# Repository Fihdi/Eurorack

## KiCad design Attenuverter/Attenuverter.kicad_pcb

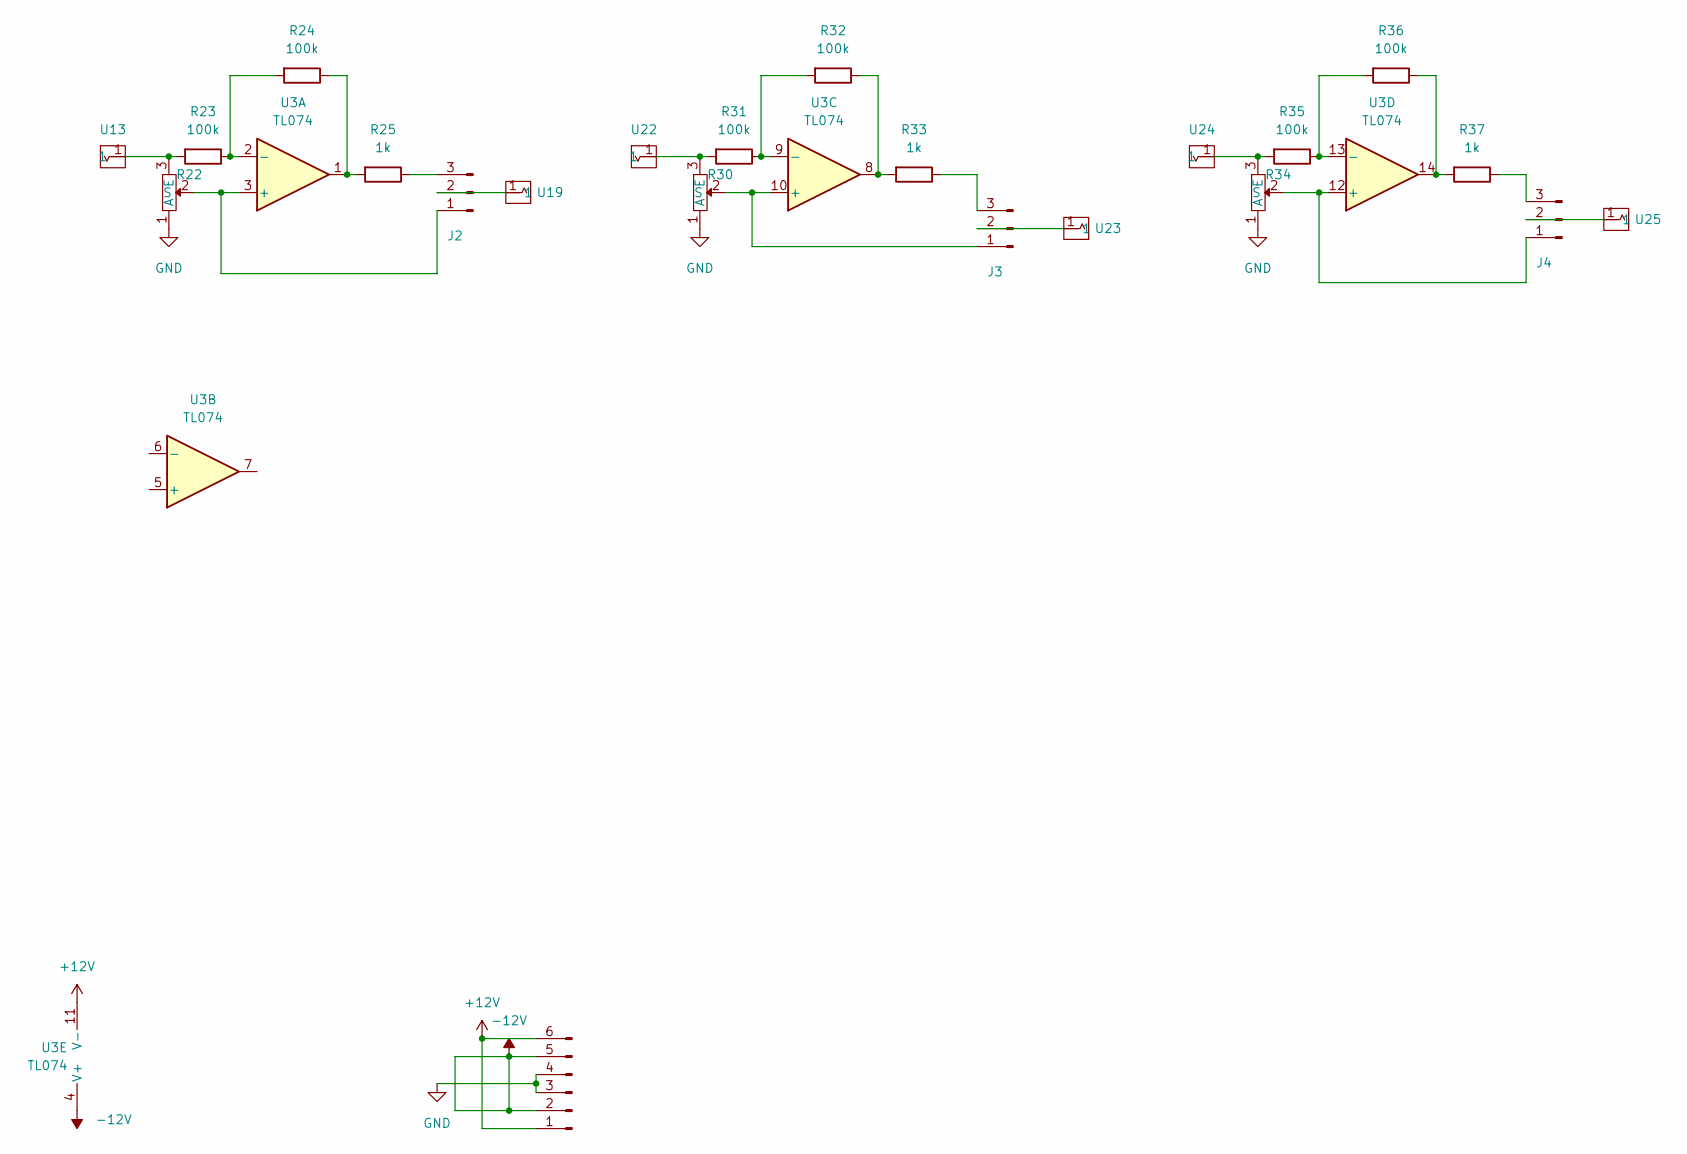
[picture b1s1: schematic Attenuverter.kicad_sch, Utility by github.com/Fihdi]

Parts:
J1: Conn_01x06_Male; PinHeader_1x06_P2.54mm_Vertical
J2, J3, J4: Conn_01x03_Pin; PinSocket_1x03_P2.54mm_Vertical
R22, R30, R34: AlpsPot
R23, R24, R31, R32, R35, R36: 100k; R_Axial_DIN0207_L6.3mm_D2.5mm_P7.62mm_Horizontal
R25, R33, R37: 1k; R_Axial_DIN0207_L6.3mm_D2.5mm_P7.62mm_Horizontal
U3: TL074; DIP-14_W7.62mm
U13, U19, U22, U23, U24, U25: Aux_flush; 3mm5 Mono Aux

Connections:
+12V: J1.1, J1.6, U3.11 (V-)
-12V: J1.2, J1.5, U3.4 (V+)
GND: J1.3, J1.4, R22.1 (A), R30.1 (A), R34.1 (A)
unnamed: J2.1, R22.2 (S), U3.3 (+)
unnamed: J2.2, U19.1
unnamed: J2.3, R25.1
unnamed: J3.1, R30.2 (S), U3.10 (+)
unnamed: J3.2, U23.1
unnamed: J3.3, R33.1
unnamed: J4.1, R34.2 (S), U3.12 (+)
unnamed: J4.2, U25.1
unnamed: J4.3, R37.1
unnamed: R22.3 (E), R23.2, U13.1
unnamed: R24.1, R25.2, U3.1
unnamed: R30.3 (E), R31.2, U22.1
unnamed: R32.1, R33.2, U3.8
unnamed: R34.3 (E), R35.2, U24.1
unnamed: R36.1, R37.2, U3.14
unnamed: R23.1, R24.2, U3.2 (-)
unnamed: R31.1, R32.2, U3.9 (-)
unnamed: R35.1, R36.2, U3.13 (-)

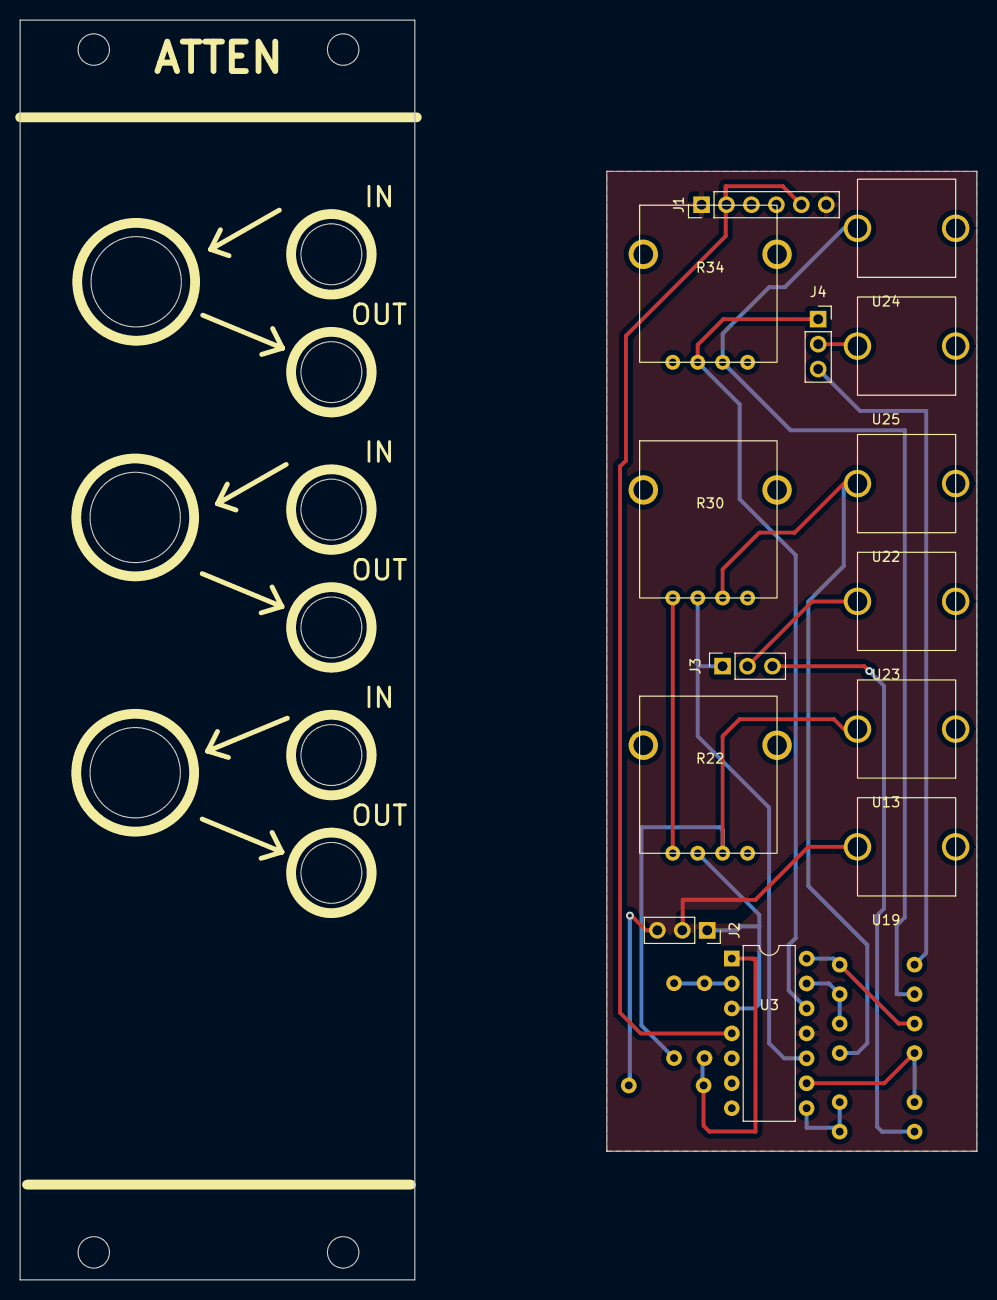
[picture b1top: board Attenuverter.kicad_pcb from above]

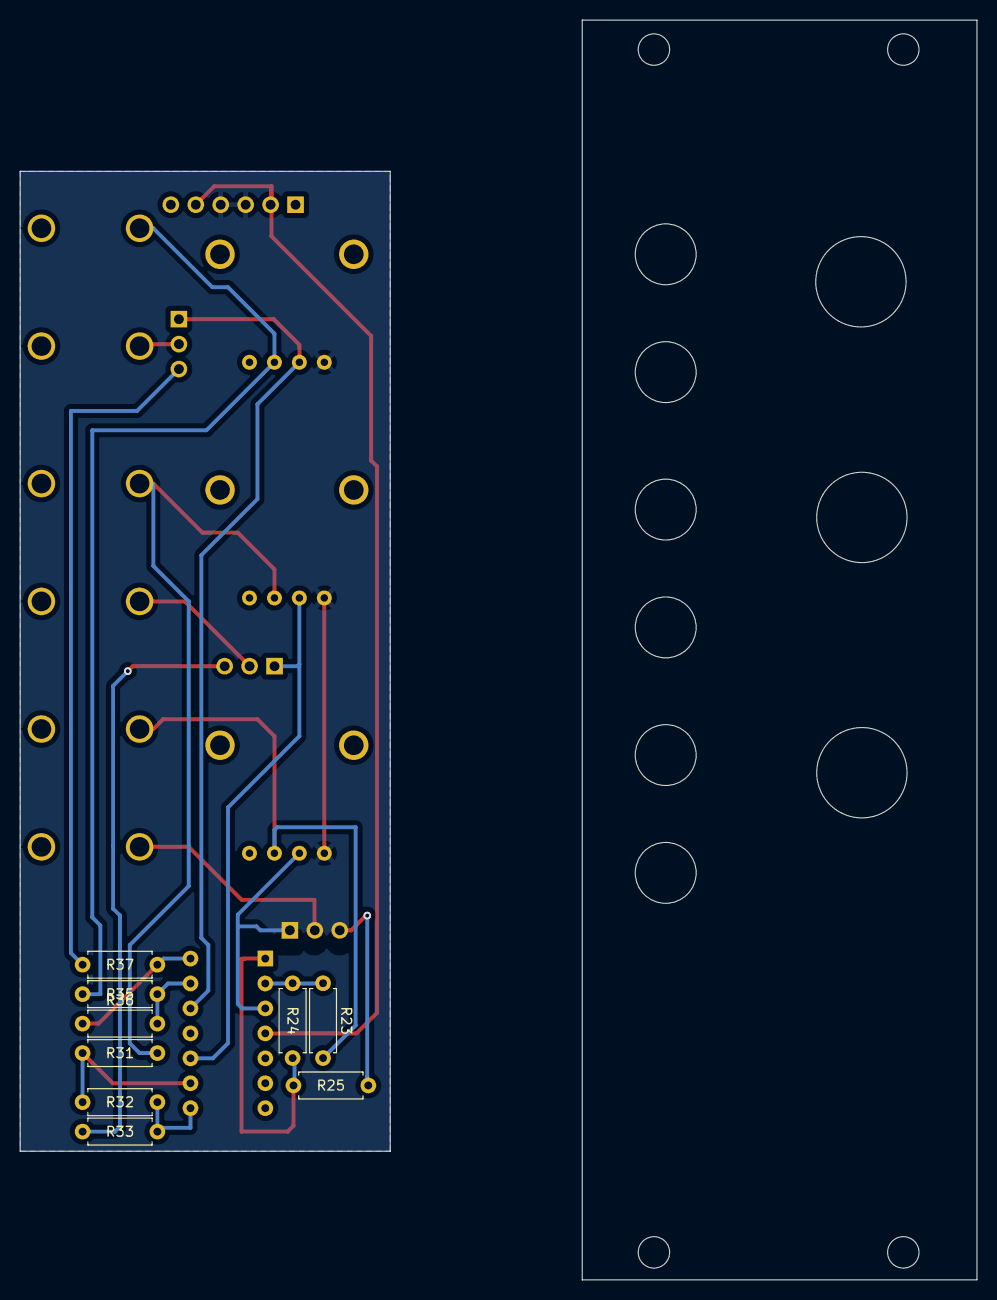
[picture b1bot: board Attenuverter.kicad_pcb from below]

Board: 2 copper layers, 37.7 x 99.8 mm, 23 parts (9 on the bottom side), 21 nets.

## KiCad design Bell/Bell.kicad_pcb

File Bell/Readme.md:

Bell Module with voltage control over decay time and accent.

Two square wave oscillators are summed together and put through a bandpass filter and a VCA. Choose the capacitor sizes of the filters and oscillators to your own liking.

No voltage control over the two square wave generator frequencies.

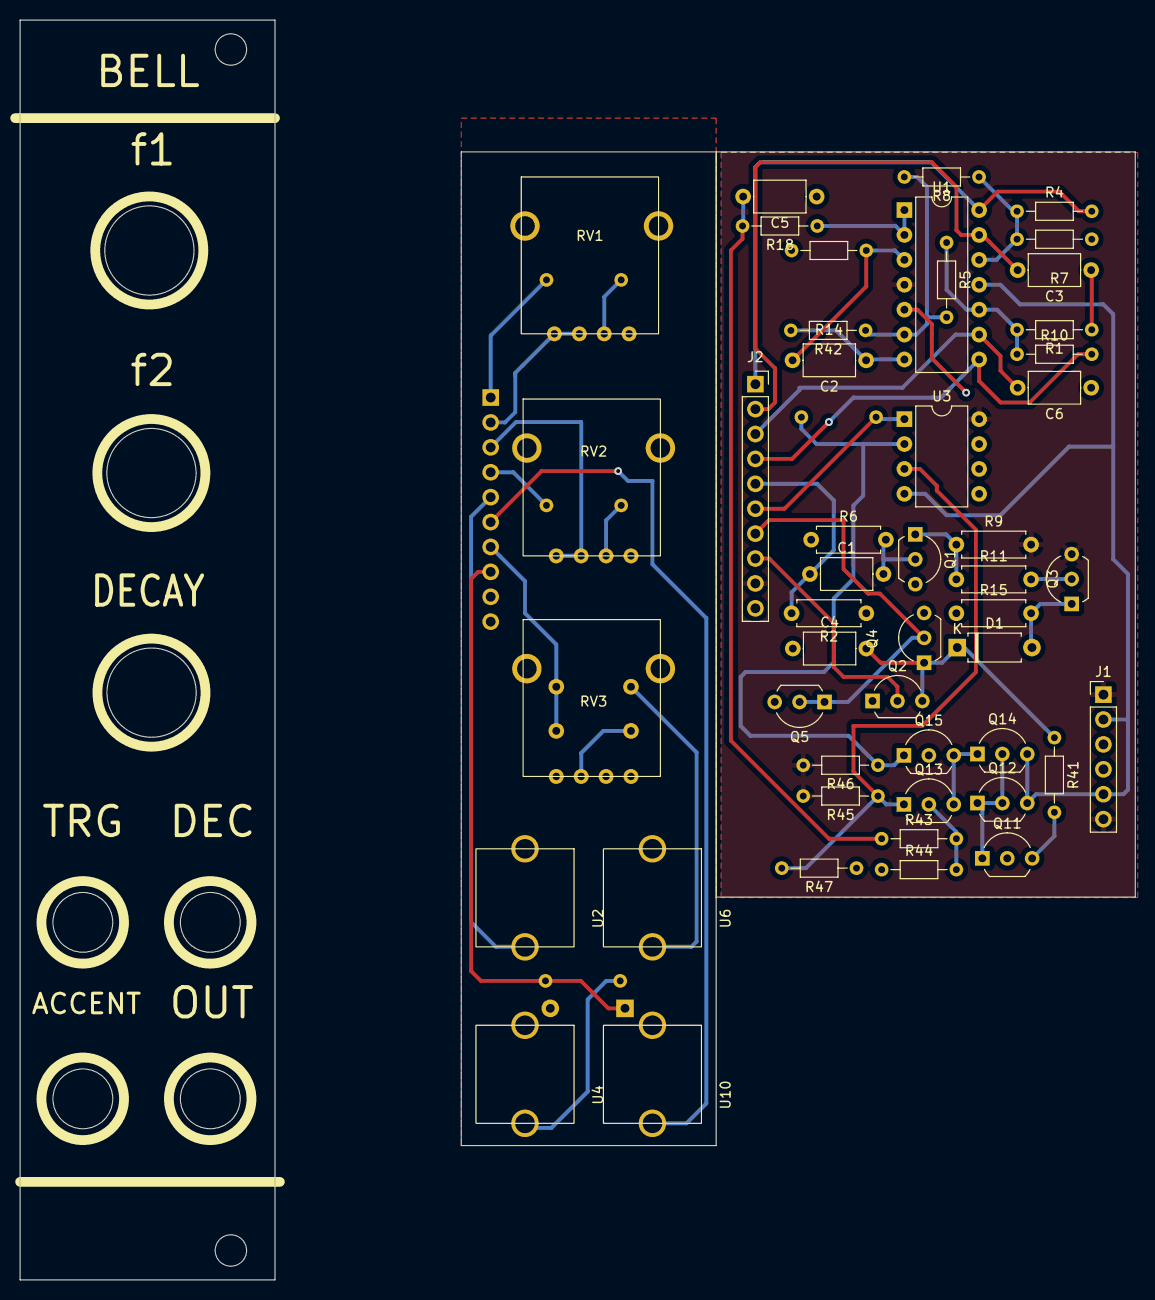
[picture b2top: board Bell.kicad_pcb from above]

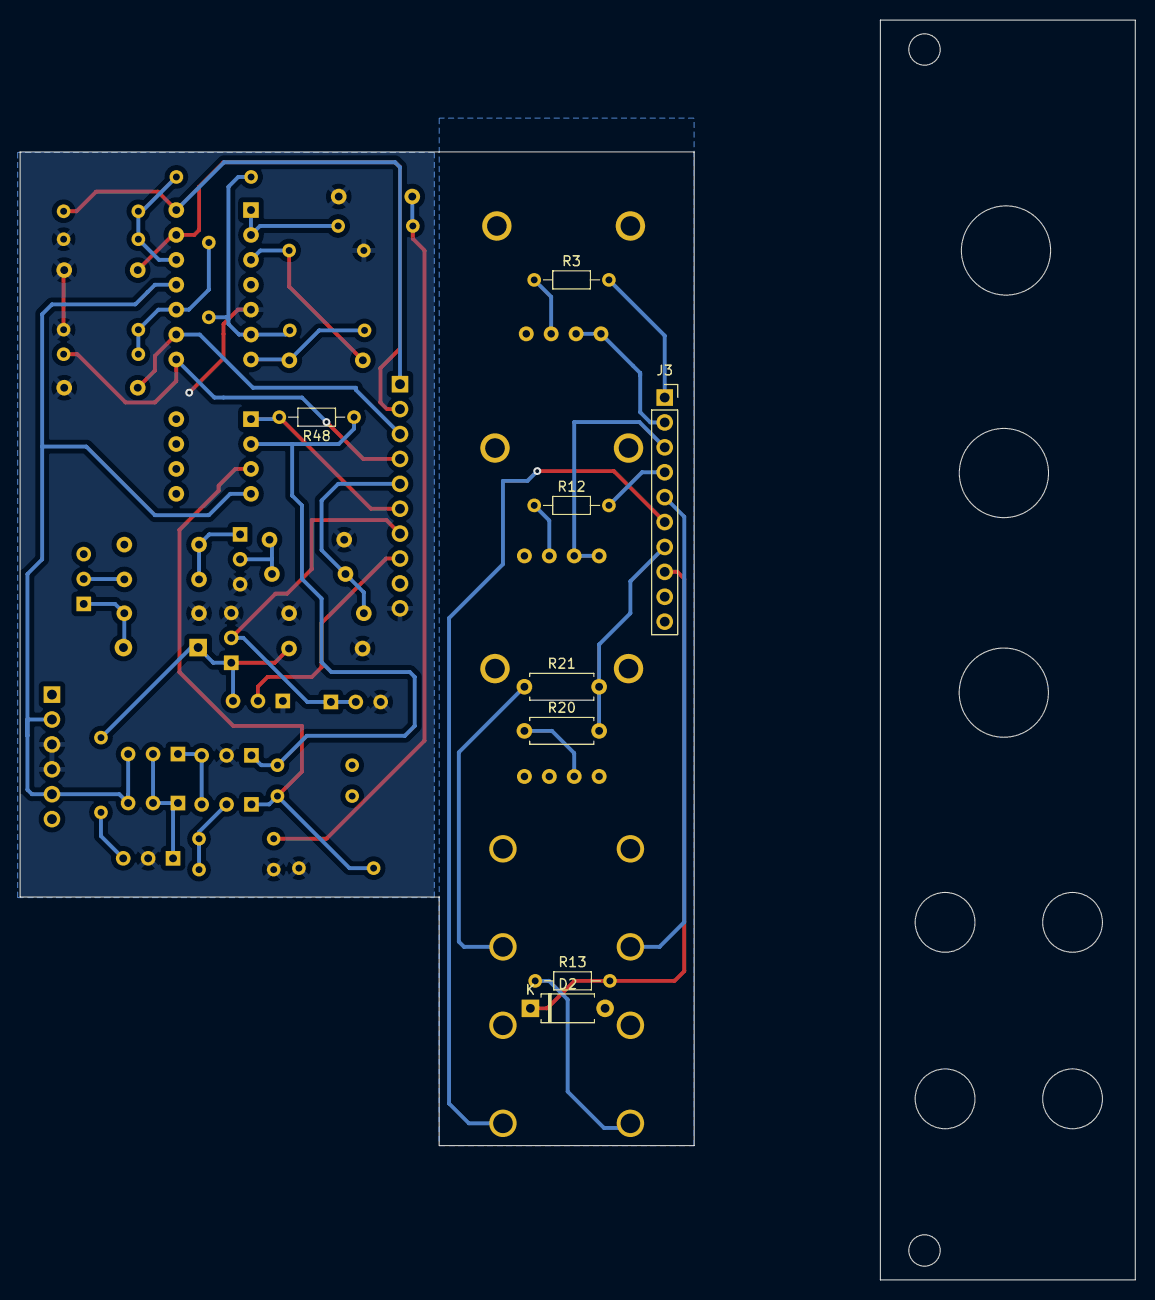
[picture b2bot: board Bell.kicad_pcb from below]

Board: 2 copper layers, 68.8 x 101.4 mm, 56 parts (8 on the bottom side), 34 nets.

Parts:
C1, C2, C3, C4, C5, C6: 5n; C_Axial_L5.1mm_D3.1mm_P7.50mm_Horizontal
D1, D2: D; D_A-405_P7.62mm_Horizontal
J1: Conn_01x06_Female; PinHeader_1x06_P2.54mm_Vertical
J2, J3: Conn_01x10_Pin; PinSocket_1x10_P2.54mm_Vertical
Q1, Q4, Q5: BC547; TO-92L_Inline_Wide
Q2, Q3: BC557; TO-92L_Inline_Wide
Q11: BC557; TO-92_Inline_Wide
Q12, Q13, Q14, Q15: BC547; TO-92_Inline_Wide
R1, R4, R5, R7, R8, R10, R14, R41, R42, R43: 100k; R_Axial_DIN0204_L3.6mm_D1.6mm_P7.62mm_Horizontal
R2, R6, R9, R15, R20, R21: 100k; R_Axial_DIN0207_L6.3mm_D2.5mm_P7.62mm_Horizontal
R3, R12, R44: 200R; R_Axial_DIN0204_L3.6mm_D1.6mm_P7.62mm_Horizontal
R11: 10k; R_Axial_DIN0207_L6.3mm_D2.5mm_P7.62mm_Horizontal
R13: 1k; R_Axial_DIN0204_L3.6mm_D1.6mm_P7.62mm_Horizontal
R18: 10k; R_Axial_DIN0204_L3.6mm_D1.6mm_P7.62mm_Horizontal
R45, R46: 50k; R_Axial_DIN0204_L3.6mm_D1.6mm_P7.62mm_Horizontal
R47, R48: 200k; R_Axial_DIN0204_L3.6mm_D1.6mm_P7.62mm_Horizontal
RV1, RV2, RV3: R_Potentiometer; AlpsPot
U1: TL074; DIP-14_W7.62mm
U2, U4, U6, U10: Aux_flush; 3mm5 Mono Aux
U3: TL072; DIP-8_W7.62mm

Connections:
+12V: J1.1, J1.6, J2.9, J3.9, Q3.3 (E), R9.2, R45.2, R46.2, RV3.3, U1.4 (V+), U3.8 (V+)
-12V: J1.2, J1.5, Q12.3 (E), Q14.3 (E), U1.11 (V-), U3.4 (V-)
ACC: D2.1 (K), J2.8, J3.8, Q2.2 (B), R13.2
BP: C5.2, R18.2, R43.1
DEC: J2.7, J3.7, Q4.2 (B), Q5.1 (C), Q5.2 (B), R20.2, R21.2
ENV: C4.2, D1.1 (K), Q2.3 (E), Q4.1 (C), R41.1
FM1: C3.2, J2.2, J3.2, RV1.1, RV1.2, U1.13 (-)
FM2: C6.2, J2.3, J3.3, RV2.1, RV2.2, U1.9 (-)
FO1: J2.1, J3.1, R3.2, R4.2, U1.14
FO2: J2.4, J3.4, R10.2, R12.2, U1.8
GND: C3.1, C4.1, C5.1, C6.1, D2.2 (A), J1.3, J1.4, J2.10, J3.10, Q1.3 (E), Q2.1 (C), Q4.3 (E), Q5.3 (E), Q11.2 (B), Q15.2 (B), R1.1, R2.1, R6.1, R7.1, R14.2, R15.1, R44.1, R47.1, RV3.1, U1.5 (+)
IN2: C1.1, J2.5, J3.5, R2.2, U2.1
unnamed: C2.1, R42.2, U1.7
unnamed: D1.2 (A), Q3.1 (C), R15.2
unnamed: C1.2, Q1.2 (B), R6.2
unnamed: Q1.1 (C), R9.1, R11.1
unnamed: Q3.2 (B), R11.2
unnamed: Q11.1 (C), Q12.1 (C), Q12.2 (B), Q14.2 (B)
unnamed: Q11.3 (E), R41.2
unnamed: Q13.2 (B), R43.2, R44.2
unnamed: Q13.1 (C), R45.1, R47.2, U3.3 (+)
unnamed: Q13.3 (E), Q14.1 (C), Q15.3 (E)
unnamed: Q15.1 (C), R46.1, R48.1, U3.2 (-)
unnamed: R3.1, RV1.3
unnamed: R12.1, RV2.3
unnamed: R13.1, U4.1
unnamed: R20.1, RV3.2
unnamed: R21.1, U6.1
unnamed: C2.2, R14.1, U1.3 (+)
unnamed: R18.1, U1.1, U1.2 (-)
unnamed: R5.2, R8.2, R42.1, U1.6 (-)
OUT: J2.6, J3.6, R48.2, U3.1, U10.1
f1: R4.1, R7.2, R8.1, U1.12 (+)
f2: R1.2, R5.1, R10.1, U1.10 (+)

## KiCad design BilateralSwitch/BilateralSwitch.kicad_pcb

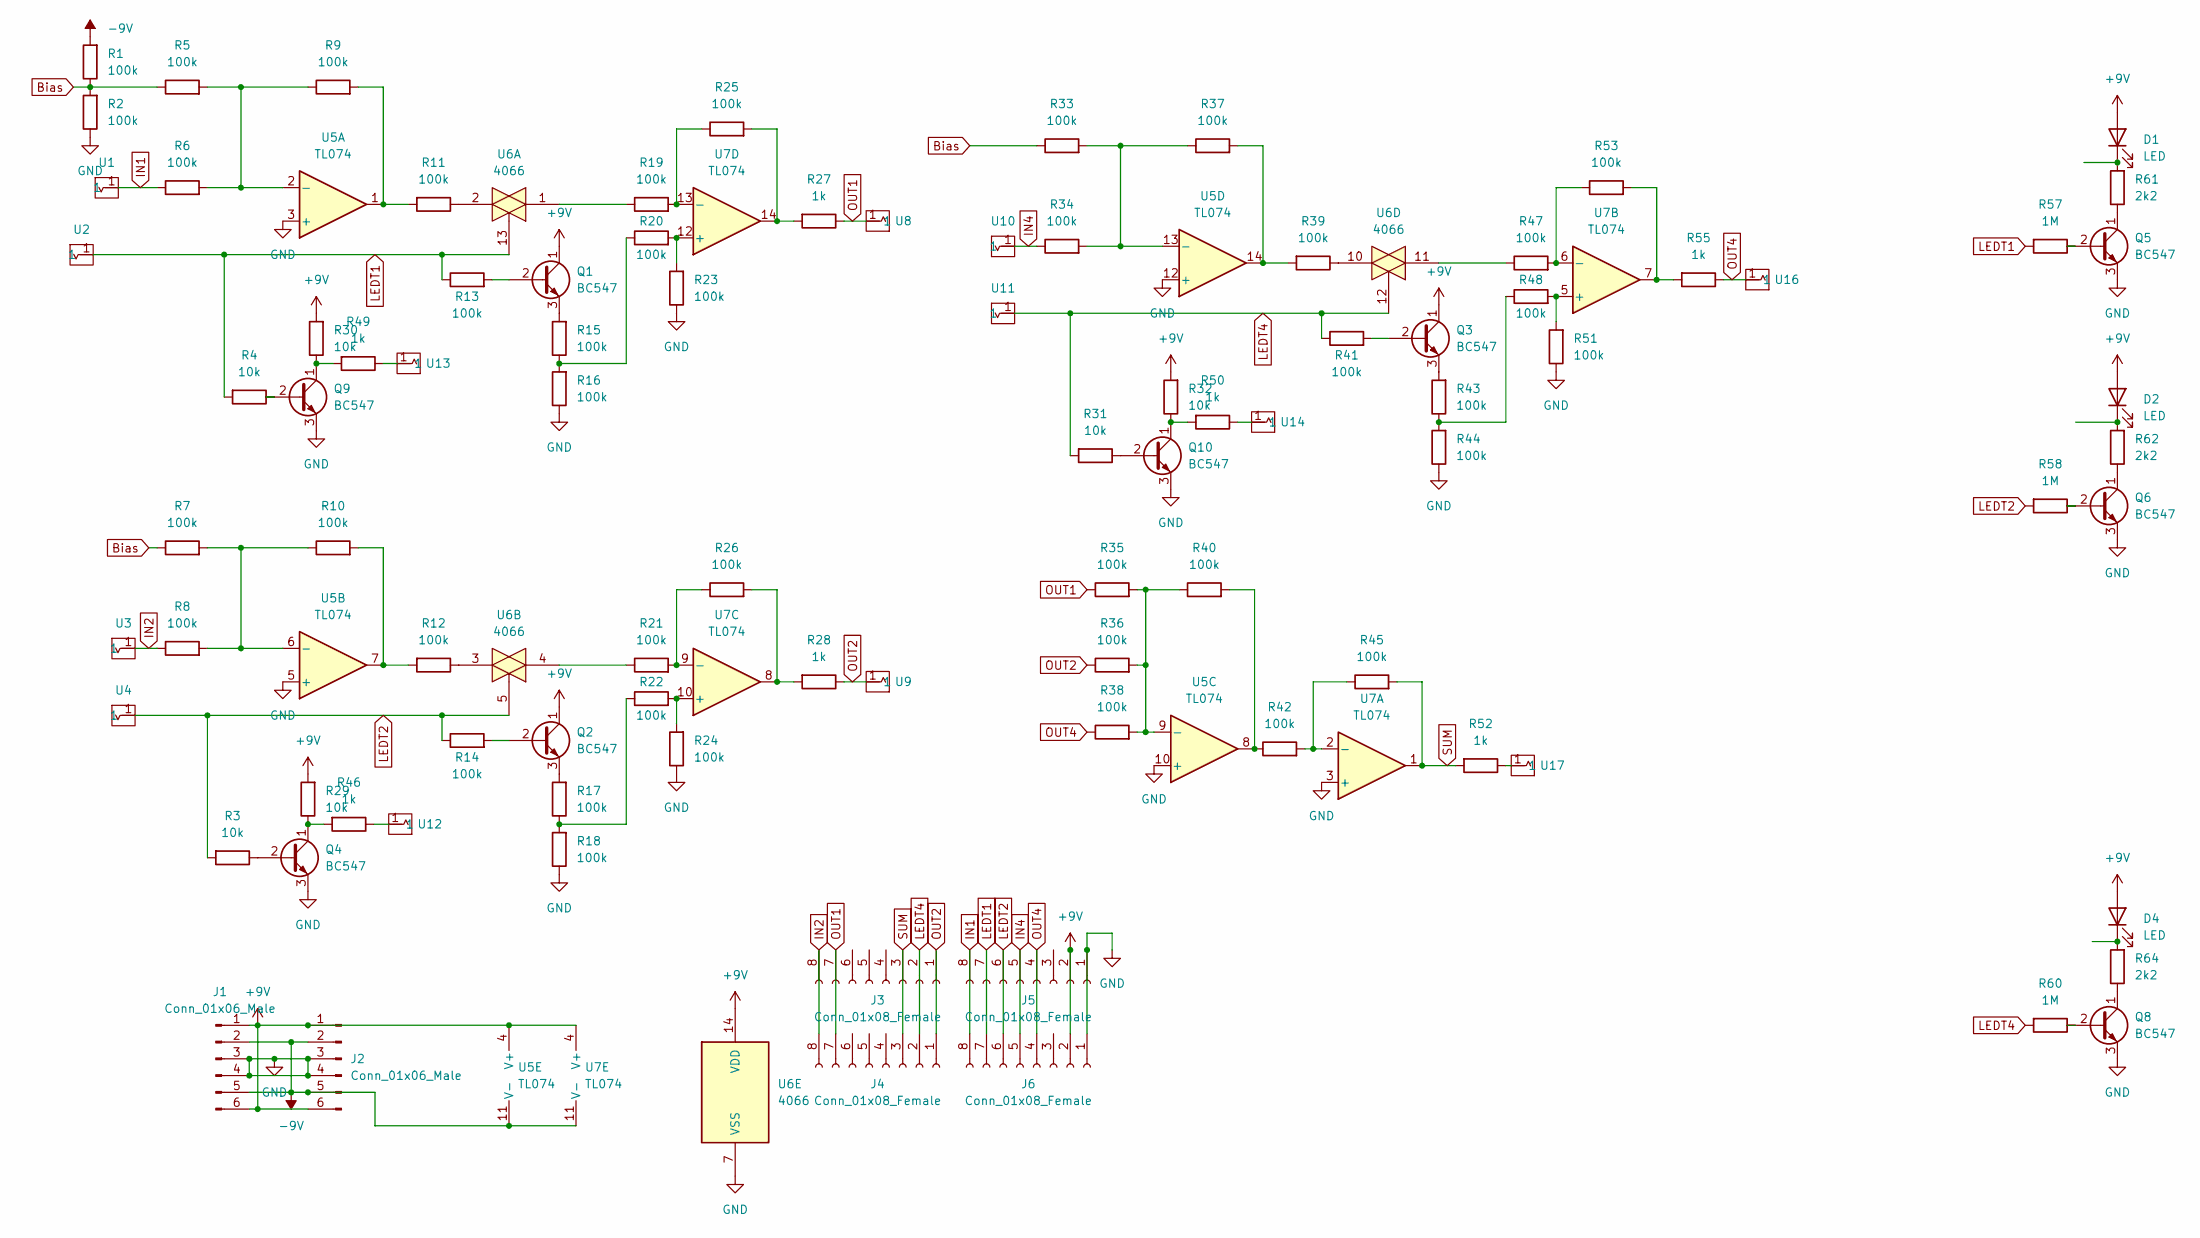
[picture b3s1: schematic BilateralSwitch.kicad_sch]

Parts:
D1, D2, D4: LED; LED_D5.0mm
J1, J2: Conn_01x06_Male; JST_EH_B6B-EH-A_1x06_P2.50mm_Vertical
J3: Conn_01x08_Female
J4, J5, J6: Conn_01x08_Female; PinHeader_1x08_P2.54mm_Vertical
Q1, Q2, Q3, Q4, Q5, Q6, Q8, Q9, Q10: BC547; TO-92_Wide
R1, R2, R5, R6, R7, R8, R9, R10, R11, R12, R13, R14, R15, R16, R17, R18, R19, R20, R21, R22, R23, R24, R25, R26, R33, R34, R35, R36, R37, R38, R39, R40, R41, R42, R43, R44, R45, R47, R48, R51, R53: 100k; R_Axial_DIN0204_L3.6mm_D1.6mm_P7.62mm_Horizontal
R3, R4, R29, R30, R31, R32: 10k; R_Axial_DIN0204_L3.6mm_D1.6mm_P7.62mm_Horizontal
R27, R28, R46, R49, R50, R52, R55: 1k; R_Axial_DIN0204_L3.6mm_D1.6mm_P7.62mm_Horizontal
R57, R58, R60: 1M; R_Axial_DIN0204_L3.6mm_D1.6mm_P7.62mm_Horizontal
R61, R62, R64: 2k2; R_Axial_DIN0204_L3.6mm_D1.6mm_P7.62mm_Horizontal
U1, U2, U3, U4, U8, U9, U10, U11, U12, U13, U14, U16, U17: Aux_flush; aux_flush
U5, U7: TL074; DIP-14_W7.62mm_Socket
U6: 4066; DIP-14_W7.62mm

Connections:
+9V: D1.2 (A), D2.2 (A), D4.2 (A), J1.1, J1.6, J2.1, J2.6, J5.2, J6.2, Q1.1 (C), Q2.1 (C), Q3.1 (C), R29.2, R30.2, R32.2, U5.4 (V+), U6.14 (VDD), U7.4 (V+)
-9V: J1.2, J1.5, J2.2, J2.5, R1.2, U5.11 (V-), U7.11 (V-)
Bias: R1.1, R2.2, R5.1, R7.1, R33.1
GND: J1.3, J1.4, J2.3, J2.4, J5.1, J6.1, Q4.3 (E), Q5.3 (E), Q6.3 (E), Q8.3 (E), Q9.3 (E), Q10.3 (E), R2.1, R16.1, R18.1, R23.1, R24.1, R44.1, R51.1, U5.3 (+), U5.5 (+), U5.10 (+), U5.12 (+), U6.7 (VSS), U7.3 (+)
IN1: J5.8, J6.8, R6.1, U1.1
IN2: J3.8, J4.8, R8.1, U3.1
IN4: J5.5, J6.5, R34.1, U10.1
LEDT1: J5.7, J6.7, R4.2, R13.1, R57.2, U2.1, U6.13
LEDT2: J5.6, J6.6, R3.2, R14.1, R58.2, U4.1, U6.5
LEDT4: J3.2, J4.2, R31.2, R41.1, R60.2, U6.12, U11.1
unnamed: D1.1 (K), R61.2
unnamed: D2.1 (K), R62.2
unnamed: D4.1 (K), R64.2
unnamed: Q1.2 (B), R13.2
unnamed: Q1.3 (E), R15.2
unnamed: Q2.2 (B), R14.2
unnamed: Q2.3 (E), R17.2
unnamed: Q3.2 (B), R41.2
unnamed: Q3.3 (E), R43.2
unnamed: Q4.1 (C), R29.1, R46.2
unnamed: Q4.2 (B), R3.1
unnamed: Q5.1 (C), R61.1
unnamed: Q5.2 (B), R57.1
unnamed: Q6.1 (C), R62.1
unnamed: Q6.2 (B), R58.1
unnamed: Q8.1 (C), R64.1
unnamed: Q8.2 (B), R60.1
unnamed: Q9.1 (C), R30.1, R49.2
unnamed: Q9.2 (B), R4.1
unnamed: Q10.1 (C), R32.1, R50.2
unnamed: Q10.2 (B), R31.1
unnamed: R5.2, R6.2, R9.1, U5.2 (-)
unnamed: R7.2, R8.2, R10.1, U5.6 (-)
unnamed: R10.2, R12.2, U5.7
unnamed: R11.1, U6.2
unnamed: R9.2, R11.2, U5.1
unnamed: R12.1, U6.3
unnamed: R15.1, R16.2, R20.1
unnamed: R17.1, R18.2, R22.1
unnamed: R19.1, U6.1
unnamed: R19.2, R25.1, U7.13 (-)
unnamed: R20.2, R23.2, U7.12 (+)
unnamed: R21.1, U6.4
unnamed: R21.2, R26.1, U7.9 (-)
unnamed: R22.2, R24.2, U7.10 (+)
unnamed: R25.2, R27.2, U7.14
unnamed: R26.2, R28.2, U7.8
unnamed: R33.2, R34.2, R37.1, U5.13 (-)
unnamed: R37.2, R39.2, U5.14
unnamed: R39.1, U6.10
unnamed: R42.2, R45.1, U7.2 (-)
unnamed: R43.1, R44.2, R48.1
unnamed: R47.1, U6.11
unnamed: R47.2, R53.1, U7.6 (-)
unnamed: R48.2, R51.2, U7.5 (+)
unnamed: R53.2, R55.2, U7.7
unnamed: R40.2, R42.1, U5.8
unnamed: R35.2, R36.2, R38.2, R40.1, U5.9 (-)
unnamed: R46.1, U12.1
unnamed: R49.1, U13.1
unnamed: R50.1, U14.1
unnamed: R52.1, U17.1
OUT1: J3.7, J4.7, R27.1, R35.1, U8.1
OUT2: J3.1, J4.1, R28.1, R36.1, U9.1
OUT4: J5.4, J6.4, R38.1, R55.1, U16.1
SUM: J3.3, J4.3, R45.2, R52.2, U7.1

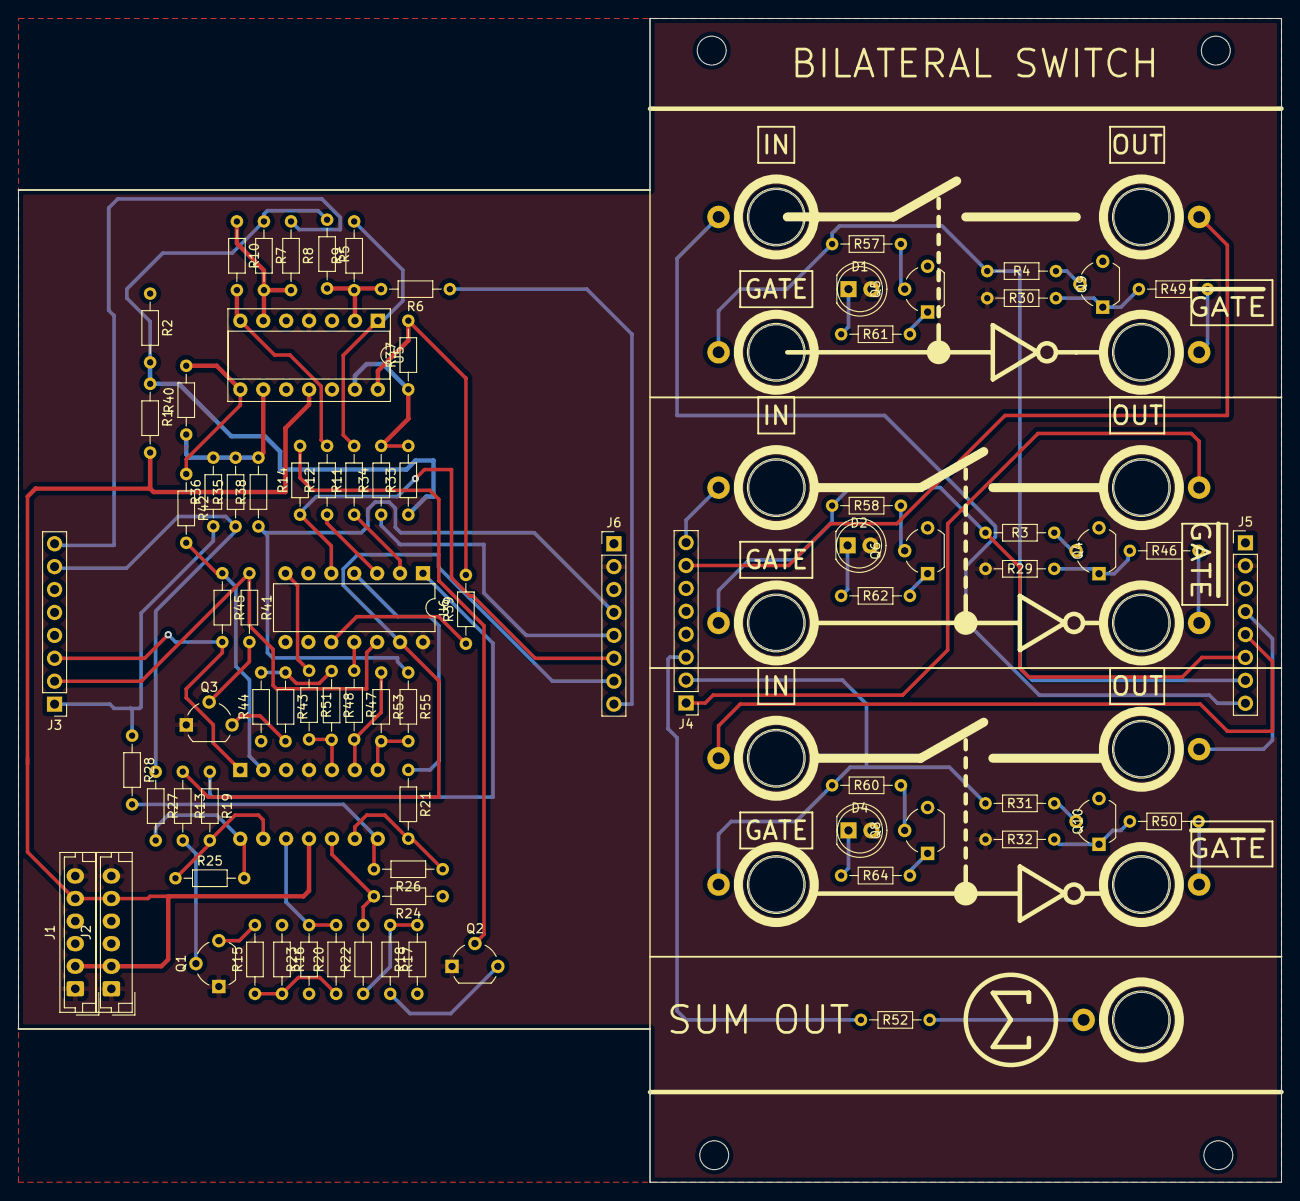
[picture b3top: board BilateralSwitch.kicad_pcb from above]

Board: 2 copper layers, 140.0 x 129.0 mm, 94 parts (1 on the bottom side), 66 nets.

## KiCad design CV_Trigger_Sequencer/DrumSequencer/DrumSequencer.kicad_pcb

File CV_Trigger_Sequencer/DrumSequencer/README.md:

No Rotary-Switch for the amount of steps.

Pulse / Trigger Outputs A, B and C have been made for the Sampler Module, but they can be used to trigger anything (Envelopes, Sample and Hold, etc)

Ideas:
One modifaction I will definitely try is to route one of the inputs (IN1 to 3) to an analog input pin of the ATMega328P. This way the stage which is active is CV-controllable. You can also programm an onboard LFO where the rate of this LFO can be CV-controlled.

Tap-tempo with an input or the push-button.

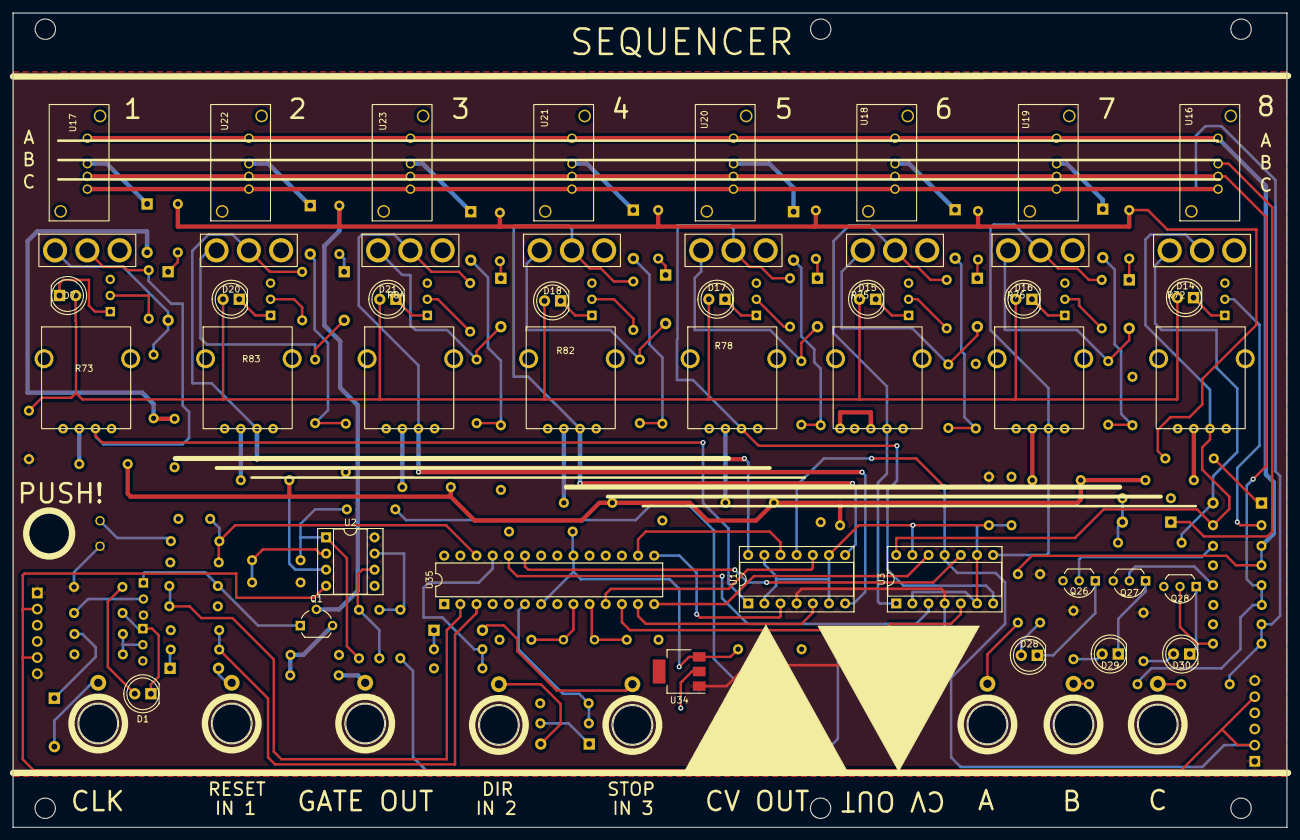
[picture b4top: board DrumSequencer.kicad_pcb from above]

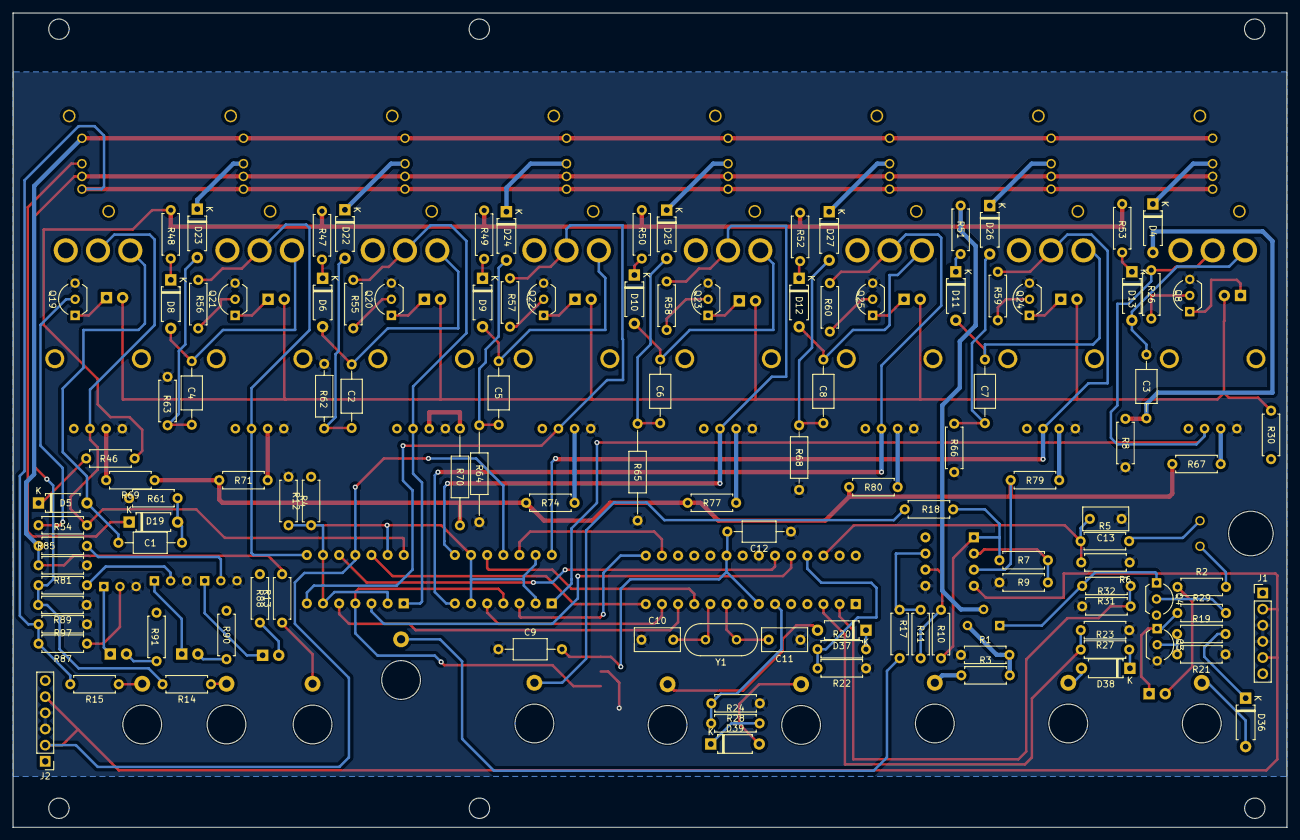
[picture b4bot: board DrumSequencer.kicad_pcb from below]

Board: 2 copper layers, 200.3 x 128.0 mm, 171 parts (115 on the bottom side), 124 nets.

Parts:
C1, C2, C3, C4, C5, C6, C7, C8, C9, C12: C; C_Axial_L5.1mm_D3.1mm_P10.00mm_Horizontal
C10, C11, C13: C; C_Rect_L7.0mm_W3.5mm_P5.00mm
D1, D7, D14, D15, D16, D17, D18, D20, D21, D28, D29, D30: LED; LED_D5.0mm
D4, D5, D6, D8, D9, D10, D11, D12, D13, D19, D22, D23, D24, D25, D26, D27, D36, D37, D38, D39: D; D_A-405_P7.62mm_Horizontal
J1, J2: Conn_01x06_Male; PinHeader_1x06_P2.54mm_Vertical
Q1: NDT3055L; TO-92_Wide
Q3: BC547; TO-92L_Inline_Wide
Q4: BC557; TO-92L_Inline_Wide
Q8, Q19, Q20, Q21, Q22, Q23, Q24, Q25, Q26, Q27, Q28: BC547; TO-92_Inline_Wide
R1, R3, R4, R7, R8, R9, R10, R11, R12, R13, R14, R15, R17, R18, R26, R30, R46, R47, R48, R49, R50, R51, R52, R53, R54, R55, R56, R57, R58, R59, R60, R61, R63, R66, R67, R69, R71, R74, R77, R79, R80, R81, R85, R86, R87, R88, R89, R90, R91, R97: R; R_Axial_DIN0207_L6.3mm_D2.5mm_P7.62mm_Horizontal
R2, R5, R6, R19, R20, R21, R22, R23, R24, R27, R28, R31, R32: 100k; R_Axial_DIN0207_L6.3mm_D2.5mm_P7.62mm_Horizontal
R29: 10k; R_Axial_DIN0207_L6.3mm_D2.5mm_P7.62mm_Horizontal
R62, R68: R; R_Axial_DIN0207_L6.3mm_D2.5mm_P10.16mm_Horizontal
R64, R65, R70: R; R_Axial_DIN0207_L6.3mm_D2.5mm_P15.24mm_Horizontal
R72, R73, R75, R76, R78, R82, R83, R84: AlpsPot
SW2: SW_Push; Push_Flush
U1, U3: TL074; DIP-14_W7.62mm_Socket
U2: TL072; DIP-8_W7.62mm_Socket
U4, U6, U7, U24, U25, U26, U30, U31, U32, U33: Aux_flush; aux_flush
U8, U9, U10, U11, U12, U13, U14, U15: Switch
U16, U17, U18, U19, U20, U21, U22, U23: SP3T
U34: LM7805_TO220; SOT-223
U35: ATmega328-P; DIP-28_W7.62mm
Y1: Crystal; Crystal_HC49-4H_Vertical

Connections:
+12V: J1.1, J1.6, J2.1, J2.6, Q4.3 (E), R2.2, R12.2, R30.2, R88.2, R90.2, R91.2, SW2.1, U1.4 (V+), U2.8 (V+), U3.4 (V+), U34.1 (VI)
-12V: J1.2, J1.5, J2.2, J2.5, U1.11 (V-), U2.4 (V-), U3.11 (V-)
A1: U1.3 (+), U35.15 (PB1)
A2: U1.12 (+), U35.16 (PB2)
A3: U1.5 (+), U35.13 (PD7)
A4: U1.10 (+), U35.11 (PD5)
A5: U3.5 (+), U35.12 (PD6)
A6: U3.3 (+), U35.24 (PC1)
A7: U3.10 (+), U35.23 (PC0)
A8: U3.12 (+), U35.14 (PB0)
CLKBUF: Q1.1 (G), Q4.1 (C), R31.2
CLKIN: D36.2 (A), U30.1
G: Q1.2 (D), R46.1, R47.1, R48.1, R49.1, R50.1, R51.1, R52.1, R53.1
GND: C9.1, C10.1, C11.1, C12.1, C13.1, J1.3, J1.4, J2.3, J2.4, Q3.3 (E), Q8.3 (E), Q19.3 (E), Q20.3 (E), Q21.3 (E), Q22.3 (E), Q23.3 (E), Q24.3 (E), Q25.3 (E), Q26.3 (E), Q27.3 (E), Q28.3 (E), R1.1, R4.1, R6.1, R8.1, R9.1, R21.1, R22.1, R27.1, R28.1, R32.1, R61.1, R62.1, R63.1, R64.1, R65.1, R66.1, R68.1, R72.1 (A), R73.1 (A), R75.1 (A), R76.1 (A), R78.1 (A), R81.1, R82.1 (A), R83.1 (A), R84.1 (A), R89.1, R97.1, U2.5 (+), U34.2 (GND), U35.8 (GND), U35.22 (GND)
IN1: R20.1, R22.2, U35.25 (PC2)
IN2: D39.2 (A), U33.1
LED: D7.2 (A), D14.2 (A), D15.2 (A), D16.2 (A), D17.2 (A), D18.2 (A), D20.2 (A), D21.2 (A), R30.1
unnamed: D1.2 (A), R2.1
unnamed: D1.1 (K), Q3.1 (C), R29.1
unnamed: C3.1, D4.2 (A), R8.2
unnamed: D4.1 (K), U17.2
unnamed: C1.2, D5.2 (A), U8.1
unnamed: D5.1 (K), R46.2
unnamed: C2.2, D6.2 (A), U9.1
unnamed: D6.1 (K), R47.2
unnamed: D7.1 (K), Q8.1 (C)
unnamed: C4.2, D8.2 (A), U10.1
unnamed: D8.1 (K), R48.2
unnamed: C5.2, D9.2 (A), U11.1
unnamed: D9.1 (K), R49.2
unnamed: C6.2, D10.2 (A), U12.1
unnamed: D10.1 (K), R50.2
unnamed: C7.2, D11.2 (A), U13.1
unnamed: D11.1 (K), R51.2
unnamed: C8.2, D12.2 (A), U14.1
unnamed: D12.1 (K), R52.2
unnamed: C3.2, D13.2 (A), U15.1
unnamed: D13.1 (K), R53.2
unnamed: D14.1 (K), Q19.1 (C)
unnamed: D15.1 (K), Q20.1 (C)
unnamed: D16.1 (K), Q21.1 (C)
unnamed: D17.1 (K), Q22.1 (C)
unnamed: D18.1 (K), Q23.1 (C)
unnamed: C1.1, D19.2 (A), R61.2
unnamed: D19.1 (K), U16.2
unnamed: D20.1 (K), Q24.1 (C)
unnamed: D21.1 (K), Q25.1 (C)
unnamed: C2.1, D22.2 (A), R62.2
unnamed: D22.1 (K), U18.2
unnamed: C4.1, D23.2 (A), R63.2
unnamed: D23.1 (K), U19.2
unnamed: C5.1, D24.2 (A), R64.2
unnamed: D24.1 (K), U20.2
unnamed: C6.1, D25.2 (A), R65.2
unnamed: D25.1 (K), U21.2
unnamed: C7.1, D26.2 (A), R66.2
unnamed: D26.1 (K), U22.2
unnamed: C8.1, D27.2 (A), R68.2
unnamed: D27.1 (K), U23.2
unnamed: D28.2 (A), R88.1
unnamed: D28.1 (K), Q26.1 (C)
unnamed: D29.2 (A), R90.1
unnamed: D29.1 (K), Q27.1 (C)
unnamed: D30.2 (A), R91.1
unnamed: D30.1 (K), Q28.1 (C)
unnamed: D36.1 (K), R19.2
unnamed: D37.2 (A), U31.1
unnamed: D37.1 (K), R20.2
unnamed: D38.1 (K), R23.2
unnamed: D39.1 (K), R24.2
unnamed: Q1.3 (S), R1.2, R3.2
unnamed: Q3.2 (B), R19.1, R21.2
unnamed: Q4.2 (B), R29.2
unnamed: Q8.2 (B), R26.1
unnamed: Q19.2 (B), R54.1
unnamed: Q20.2 (B), R55.1
unnamed: Q21.2 (B), R56.1
unnamed: Q22.2 (B), R57.1
unnamed: Q23.2 (B), R58.1
unnamed: Q24.2 (B), R59.1
unnamed: Q25.2 (B), R60.1
unnamed: Q26.2 (B), R85.1
unnamed: Q27.2 (B), R86.1
unnamed: Q28.2 (B), R87.1
unnamed: R3.1, U4.1
unnamed: R5.2, SW2.2
unnamed: R7.2, R10.2, R18.1, U2.1
unnamed: R11.1, R17.1, U2.7
unnamed: R13.1, U24.1
unnamed: R13.2, R81.2, R85.2, U16.1, U17.1, U18.1, U19.1, U20.1, U21.1, U22.1, U23.1
unnamed: R14.1, U25.1
unnamed: R14.2, R86.2, R89.2, U16.3, U17.3, U18.3, U19.3, U20.3, U21.3, U22.3, U23.3
unnamed: R15.1, U26.1
unnamed: R15.2, R87.2, R97.2, U16.4, U17.4, U18.4, U19.4, U20.4, U21.4, U22.4, U23.4
unnamed: R17.2, U7.1
unnamed: R18.2, U6.1
unnamed: R54.2, R72.3 (E), U3.14, U8.2
unnamed: R69.2, R72.2 (S)
unnamed: R26.2, R73.3 (E), U1.1, U15.2
unnamed: R67.2, R73.2 (S)
unnamed: R55.2, R75.3 (E), U3.1, U9.2
unnamed: R70.2, R75.2 (S)
unnamed: R56.2, R76.3 (E), U3.8, U10.2
unnamed: R71.2, R76.2 (S)
unnamed: R57.2, R78.3 (E), U3.7, U11.2
unnamed: R74.2, R78.2 (S)
unnamed: R58.2, R82.3 (E), U1.8, U12.2
unnamed: R77.2, R82.2 (S)
unnamed: R59.2, R83.3 (E), U1.14, U13.2
unnamed: R79.2, R83.2 (S)
unnamed: R60.2, R84.3 (E), U1.7, U14.2
unnamed: R80.2, R84.2 (S)
unnamed: R7.1, R9.2, U2.2 (-)
unnamed: R10.1, R11.2, U2.6 (-)
unnamed: C9.2, C12.2, U34.3 (VO), U35.7 (VCC), U35.20 (AVCC)
unnamed: C13.2, R5.1, R6.2, U35.26 (PC3)
unnamed: R31.1, R32.2, U35.2 (PD0)
unnamed: R23.1, R27.2, U35.3 (PD1)
unnamed: R24.1, R28.2, U35.6 (PD4)
unnamed: C11.2, U35.9 (XTAL1/PB6), Y1.1
unnamed: C10.2, U35.10 (XTAL2/PB7), Y1.2
RSTIN: D38.2 (A), U32.1
THR: R4.2, R12.1, U1.2 (-), U1.6 (-), U1.9 (-), U1.13 (-), U3.2 (-), U3.6 (-), U3.9 (-), U3.13 (-)
X: R67.1, R69.1, R70.1, R71.1, R74.1, R77.1, R79.1, R80.1, U2.3 (+)
